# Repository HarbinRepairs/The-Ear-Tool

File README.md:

# The Ear Tool

Model: ET-1

Get this kit at our store: http://bit.ly/2TQ3Cbr
Or on eBay: https://ebay.to/38sRZv4

# License
Harbin Repairs 2020
Creative Commons Attribution ShareAlike 4.0
https://creativecommons.org/licenses/by-sa/4.0/

# Documentation

## What is the Ear tool?
The Ear tool can be used to detect almost any electromagnetic interference coming from your electronics such as a power supply, transformer, CPU, microcontroller, wireless transmitter, relays, switches, speakers, transducers, transistors and more. At Harbin Repairs we use the Ear Tool to diagnose problems with computer motherboards, cellphones, and televisions by pointing the tool at different parts of a circuit board and listening to the high frequency pulsing coming from different components. For example, this can help us determine if a CPU or microcontroller is doing any processing or if it’s just sitting there burning up because there’s a short somewhere. It can also let us know if a cellphone or other device is turning on even if there’s no sign of life on the screen or lights. The tool can also be used to discover the different noises your electronics make when they are doing different things (e.g. standby mode vs. fully powered on). For the controls, the gain switch adjusts between high and low sensor gain and the full scope switch switch is used to help clear up some of the background noise. More examples are in the assembly guide video below.
## Demonstration and kit assmebly guide Video

https://youtu.be/0QIx8OhJN-o

## Bill of Materials

| Description                   | Part #             | Main Links (Affiliate)      | eBay Links (Affiliate)  | Amazon Links (Affiliate) |
|-------------------------------|--------------------|-----------------------------|-------------------------|--------------------------|
| PCB                           | N/A                | PCB manufacturer of choice  | N/A                     | N/A                      |
| Enclosure                     | 1591BSBK           | https://bit.ly/2sKEk3i      | https://ebay.to/30SXp05 | https://amzn.to/2um65Qa  |
| Speaker                       | 1.5W8R 8R1.5W      | https://bit.ly/2upP8nP      | https://ebay.to/36eXlbX | N/A                      |
| 100Ω Resistor 0805            | N/A                | https://bit.ly/2TKRSqF      | https://ebay.to/2ul6eDt | N/A                      |
| 1kΩ Resistor 0805             | N/A                | https://bit.ly/36lOaql      | https://ebay.to/2TNRTtY | N/A                      |
| 220uf Electrolytic Capacitor  | N/A                | https://bit.ly/2RxIeEY      | https://ebay.to/2RHrTh0 | N/A                      |
| 4.7uf Ceramic Capacitor 0805  | N/A                | https://bit.ly/3awu9k3      | https://ebay.to/36lOJ3r | N/A                      |
| Blue LED 5mm                  | N/A                | https://bit.ly/2GgnU5K      | https://ebay.to/37h1f5p | https://amzn.to/37sNP6c  |
| LM386 Audio Amp               | LM386              | https://bit.ly/2tweNeR      | https://ebay.to/2RHXmA1 | N/A                      |
| SPST Slide Switch THT         | SS12F17G4          | https://bit.ly/30IrAqm      | https://ebay.to/30MXx14 | N/A                      |
| 3.5mm Headphone Jack          | 307 3F07           | https://bit.ly/36hQ5Mu      | https://ebay.to/36eJQcm | https://amzn.to/36eYmRj  |
| 100mH Inductor                | N/A                | https://bit.ly/38xpU63      | https://ebay.to/36eJQJo | https://amzn.to/2TNTjoi  |
| Felt Tape                     | JVCC FELT-065      | https://ebay.to/2G9WzlS     | https://ebay.to/2G9WzlS | https://amzn.to/30JB05h  |
| Battery Compartment Separator | Custom Laser Cut   | https://www.delviesplastics.com/ | Drawings available on Github | N/A                      |
| 9v Battery Clip               | N/A                | https://bit.ly/2RfzFjh      | https://ebay.to/2uis6zx | https://amzn.to/2TKSEnB  |
| 10KΩ Potentiometer            | B103 10K 0932 WH09 | https://bit.ly/2ul666X      | https://ebay.to/2NRkgno | N/A                      |
| Pot Knob 15mm x 17mm x 6mm    | N/A                | https://bit.ly/37f6bYo      | https://ebay.to/37jvYim | https://amzn.to/2GawAur  |
| Terminal Block Connector      | KF301-5.0-2P       | https://bit.ly/38xsJnF      | https://ebay.to/3avkOZG | https://amzn.to/369tQZ2  |

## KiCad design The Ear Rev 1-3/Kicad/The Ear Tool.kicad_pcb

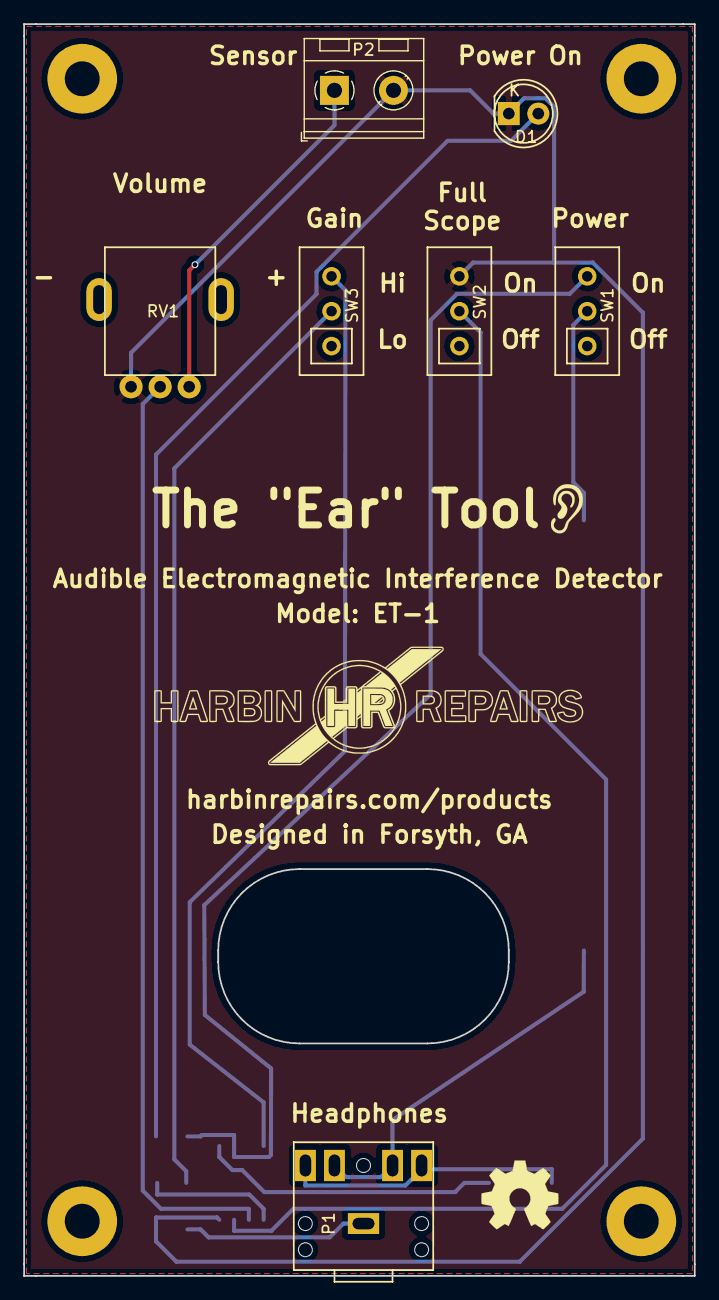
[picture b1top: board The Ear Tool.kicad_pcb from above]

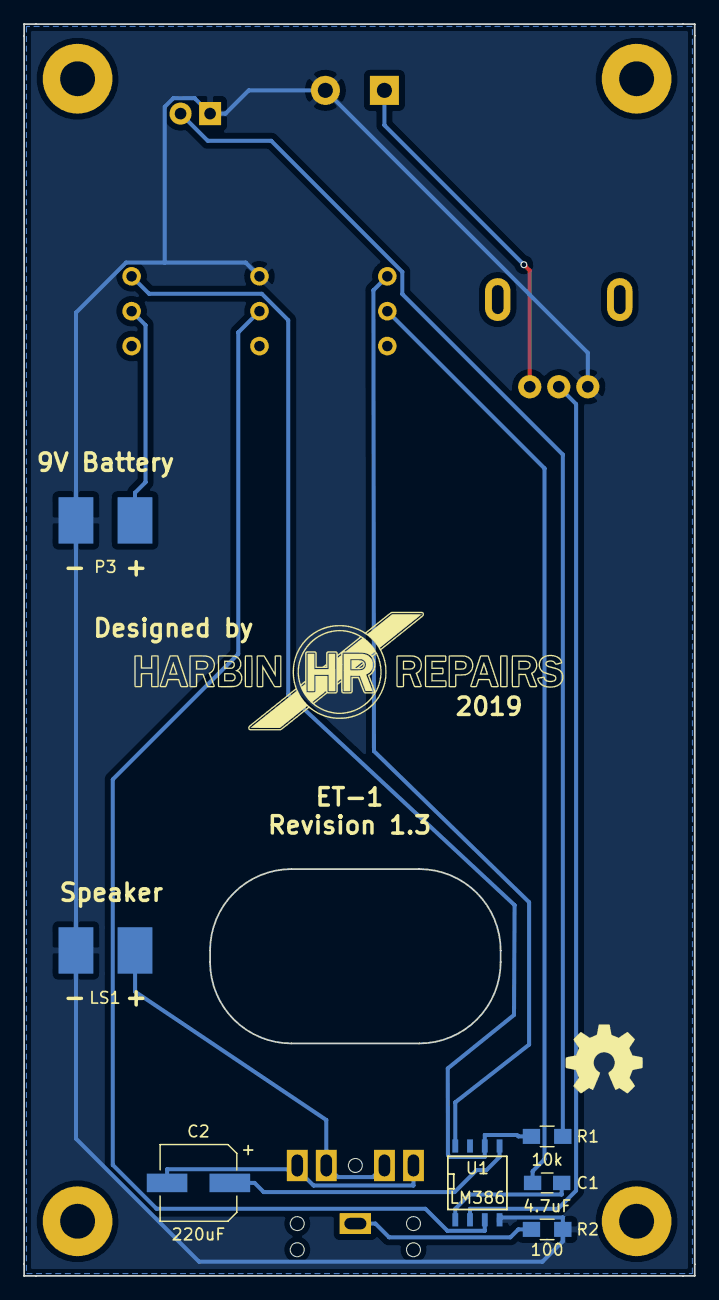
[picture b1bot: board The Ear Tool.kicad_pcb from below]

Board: 2 copper layers, 57.7 x 107.7 mm, 21 parts (8 on the bottom side), 14 nets.

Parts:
C1: 4.7uF; C_0805_HandSoldering
C2: 220uF; CP_Elec_6.3x7.7
D1: LED; LED-5MM
G1, G2: LOGO; HR_LOGO_37.4x10.6mm
G3: LOGO; Ear_icon_4.2x4.2mm
LS1: Speaker; NetTie-I_SMD
M1, M2, M3, M4: MountingHole_3mm_Pad
P1: AUDIO-JACK-3F07-TRS
P2: Sensor Connector; TerminalBlock_RND_205-00232_Pitch5.08mm
P3: 9V Battery Clip; NetTie-I_SMD
R1: 10k; R_0805_HandSoldering
R2: 100; R_0805_HandSoldering
RV1: 10k; POT_RV09_HORIZONTAL_WHO9
SW1: Power Switch; SW_SPDT_3P_11.1mm_5.5mm
SW2: Full Scope Switch; SW_SPDT_3P_11.1mm_5.5mm
SW3: Gain Switch; SW_SPDT_3P_11.1mm_5.5mm
U1: LM386; SOIC-8-N

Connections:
+9V: P3.1, SW1.2
GND: D1.1, LS1.1, P2.2, P3.2, R2.2, RV1.1, SW2.3, U1.4
unnamed: C1.1, U1.1
unnamed: C1.2, SW3.2
unnamed: C2.1, U1.5
unnamed: C2.2, P1.2, P1.5
unnamed: D1.2, R1.1
unnamed: LS1.2, P1.3, P1.4
unnamed: P1.1, R2.1
unnamed: P2.1, RV1.3
unnamed: R1.2, SW1.3, U1.6
unnamed: SW2.2, U1.3
unnamed: SW3.3, U1.8
SENSE: RV1.2, U1.2
